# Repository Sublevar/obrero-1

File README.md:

# obrero-1

Secuenciador MIDI de pasos en Rust, con doble target: **ESP32** (MIDI DIN por UART) y **web** (WASM + Web MIDI API). Toda la lógica vive en un core portable; las plataformas solo aportan tiempo e I/O.

## Arquitectura

```
crates/obrero-core    Motor sans-io: parser MIDI, patrón, transporte, reloj 480 PPQN.
                      Sin threads ni I/O — la plataforma llama advance(now, lookahead)
                      y recibe eventos MIDI timestampeados. Testeable en host.
crates/obrero-wasm    Bindings wasm-bindgen del motor para el navegador.
web/                  UI TypeScript (vite): grilla de pasos, Web MIDI, scheduler
                      con lookahead de 100 ms y send timestampeado.
firmware/             Binario ESP32 (esp-idf-svc, toolchain xtensa propio).
                      Excluido del workspace raíz — se compila aparte.
```

- Reloj interno (master, emite 0xF8/Start/Stop) o externo (esclavo de MIDI clock entrante).
- Resolución interna 480 PPQN (ver "Resolución temporal"); el MIDI clock sigue a 24 PPQN y un paso de semicorchea = 120 ticks.
- `MIDI-DIN.md` documenta el hardware DIN (6N137, UART2 a 31250 bps).
- [PPQN](https://noiseengineering.us/blogs/loquelic-literitas-the-blog/getting-started-clocks/)
## Resolución temporal (PPQN)

PPQN (*pulses per quarter note*) es cuántos ticks internos caben en una negra: la grilla más fina en la que el motor puede ubicar una nota, medir un gate o repartir una subdivisión. El motor cuenta todo en ticks (`pattern::PPQN`, definido en `tuning.rs`); el tempo solo cambia cuánto dura cada tick.

Se fija en **480** porque es divisible por 24 (el MIDI clock sigue saliendo a 24 PPQN: un `0xF8` cada 20 ticks) y por 3, 4, 5, 8, 16…, así que tresillos, quintillos y micro-timing caen en ticks enteros. A 120 bpm un tick dura ~1,04 ms; a 300 bpm, ~208 µs.

Cuesta performance: a 300 bpm son 2400 ticks por segundo que el reloj genera y el motor procesa, y los rings (más abajo) crecen en proporción. El PPQN puede **reducirse** (p. ej. a 96 o 24) para ganar performance, sobre todo en el ESP32, a costa de granularidad y resolución del micro-timing. Debe seguir siendo múltiplo de 24; los demás topes se recalculan solos al cambiarlo.

## Ajustes (fine tuning)

Todas las variables de ajuste viven en `crates/obrero-core/src/tuning.rs`. Los tamaños de ring se derivan de las demás, así que cambiar una mantiene coherente al resto.

| Variable | Valor | Qué controla / qué pasa si se cambia |
|---|---|---|
| `PPQN` | 480 | Resolución interna. Más alto: más fino y más costoso. Debe ser múltiplo de `MIDI_CLOCK_PPQN`. |
| `MIDI_CLOCK_PPQN` | 24 | Resolución del `0xF8`. Fijada por el estándar MIDI. |
| `MIN_BPM` / `MAX_BPM` | 20 / 300 | Rango de tempo. `MAX_BPM` dimensiona los rings (peor caso). |
| `MAX_SUBS` | 32 | Suscripciones simultáneas a un `Clock`. Superado: `ClockError::Full`. |
| `PER_BAR_MAX` | 96 | Tope de `Subdivision::PerBar`. Dimensiona `NOTICE_CAPACITY`. |
| `EVERY_N_BARS_MAX` | 8 | Tope de `Subdivision::EveryNBars`. |
| `MAX_CATCHUP_US` | 100 000 | Atraso que el reloj recupera tick por tick. Más allá salta hacia adelante (`skipped_ticks`) en vez de emitir una ráfaga. |
| `MAX_LOOKAHEAD_US` | 100 000 | Lookahead por pasada que los rings cubren. `Engine::advance` parte lookaheads mayores en pasadas de este tamaño. La web usa 100 ms; el ESP32, 0. |
| `RING_MARGIN` | 4 | Holgura sumada al peor caso de cada ring, antes de redondear a potencia de 2. |
| `EXTERNAL_SMOOTHING` | 4 | Clock externo: el período entre `0xF8` se suaviza como `(anterior · (N − 1) + medido) / N`. Más alto filtra más jitter y sigue más lento los cambios de tempo. |
| `NOTICE_CAPACITY` | derivada (32) | Ring por defecto de una suscripción: avisos de `PerBar(PER_BAR_MAX)` en `MAX_CATCHUP_US + MAX_LOOKAHEAD_US` a `MAX_BPM`, redondeado a potencia de 2 (índice con máscara, sin división). 512 B por suscripción; se aloja al suscribir, no en el camino caliente. |
| `ENGINE_RING_CAPACITY` | derivada (512) | Ring de la suscripción del `Engine` (un aviso por tick base) en la misma ventana, potencia de 2: 8 KiB (16 B por aviso). Con estos topes no puede desbordar; `Engine::lost_ticks()` lo verifica y debe ser 0. |

Si un ring llega a llenarse, el aviso nuevo se descarta y se cuenta (`Subscription::take` devuelve los perdidos); nunca se pierde en silencio. Para un uso concreto se puede pedir otro tamaño con `Clock::subscribe_with_capacity` (se redondea a la siguiente potencia de 2).

La memoria la fija la ventana (`MAX_CATCHUP_US + MAX_LOOKAHEAD_US`), no el PPQN: duplicar la ventana duplica el ring del `Engine` (512 → 1024 → 2048 avisos, 8 → 16 → 32 KiB). En el ESP32-S3 conviene dejarla corta. El reloj externo (`0xF8`) también pasa por el `Clock`: el tempo se mide con el período entre pulsos y cada pulso reparte sus 20 ticks parejo, sin esperar al pulso siguiente.

## Workspace raíz (stable)

```sh
# Tests del motor (host)
cargo test -p obrero-core

# Build WASM
cargo build -p obrero-wasm --target wasm32-unknown-unknown
```

## Web

Requiere `wasm-pack` (`cargo install wasm-pack`) y Node.

```sh
cd web
npm install
npm run wasm   # compila crates/obrero-wasm → web/src/pkg
npm run dev    # http://localhost:5173 (Web MIDI requiere Chrome/Edge)
```

Elegí una salida MIDI (sintetizador, DAW o loopback virtual) y dale Play. Para modo esclavo, seleccioná una entrada MIDI y reloj "Externo".

## Firmware ESP32

Tiene su propio toolchain (`esp`, fork Xtensa — ver `firmware/rust-toolchain.toml`) y ESP-IDF v5.3.3 via embuild.

```sh
# Setup (una vez)
cargo install espup && espup install
source ~/export-esp.sh   # agregar al perfil de shell
cargo install espflash

cd firmware

cargo build              # primera build descarga ESP-IDF en .embuild/ — tarda
./dev.sh                 # build + flash + monitor por el conector UART del devkit

./dev.sh -p /dev/ttyUSB1 # elegir puerto serie a mano

./dev.sh -m esp32        # flashear el binario de la board ESP32 clásica

```

`dev.sh -m` solo elige qué directorio de target flashear — el chip compilado lo define `.cargo/config.toml`.

### USB-MIDI + debug serial (dos cables)

El firmware S3 levanta TinyUSB (componente `espressif/esp_tinyusb`, ver
`Cargo.toml` y `CONFIG_TINYUSB_MIDI_COUNT` en `sdkconfig.defaults`) sobre el
puerto **USB nativo** (GPIO19/20), que enumera como dispositivo USB-MIDI.
Los logs y el flasheo van por el conector **UART** (bridge USB-UART → UART0),
así que conviene tener ambos cables conectados: `dev.sh` flashea y monitorea
solo por `/dev/ttyUSB*` y deja el `/dev/ttyACM*` (USB nativo) libre para MIDI.

Al usar USB-OTG se pierde el USB-Serial-JTAG del puerto nativo (comparten PHY);
el debug queda en el conector UART. TinyUSB no compila para el ESP32 clásico
(no tiene USB-OTG): para ese chip hay que comentar el bloque
`extra_components` en `firmware/Cargo.toml`.

Flasheo manual según target activo:

```sh
# ESP32 (rev1)
espflash flash target/xtensa-esp32-espidf/debug/obrero-1 && espflash monitor

# ESP32-S3
espflash flash target/xtensa-esp32s3-espidf/debug/obrero-1 && espflash monitor
```

## Entorno de testeo

[Web MIDI Tester](https://studiocode.dev/webmidi-tester/midi)

## Licencia

[GPL-3.0-or-later](LICENSE) — © 2026 Pablo Labarta <pablitolabarta@gmail.com> & Santiago Fernandez <stfg.prof@gmail.com>.

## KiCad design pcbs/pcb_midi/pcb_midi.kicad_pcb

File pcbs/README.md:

Ajustar la configuración de backups (KiCad V10 o +)

En las versiones más recientes (KiCad V10), KiCad tiene un sistema de control de versiones local que crea la carpeta .history. Puedes desactivar esta función para que no se genere en primer lugar:

Abre KiCad y ve al menú Preferencias → Preferencias.
Busca la sección Control de versiones.
Desmarca la opción "Habilitar seguimiento Git" (o similar, "Enable Git tracking").
Ten en cuenta que, aunque desactives esta opción, es muy recomendable mantener la carpeta .history en tu .gitignore como respaldo.

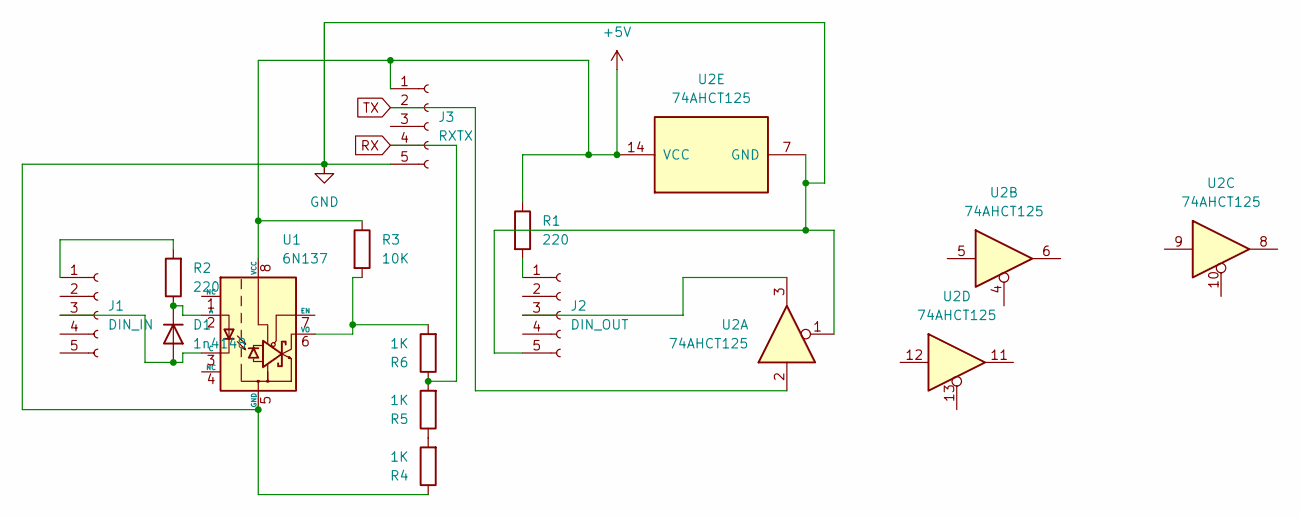
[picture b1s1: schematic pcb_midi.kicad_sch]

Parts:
D1: 1n4148; D_A-405_P10.16mm_Horizontal
J1: DIN_IN; JST_EH_B5B-EH-A_1x05_P2.50mm_Vertical
J2: DIN_OUT; JST_EH_B5B-EH-A_1x05_P2.50mm_Vertical
J3: RXTX; JST_EH_B5B-EH-A_1x05_P2.50mm_Vertical
R1: 220; R_Axial_DIN0207_L6.3mm_D2.5mm_P10.16mm_Horizontal
R2: 220; R_Axial_DIN0204_L3.6mm_D1.6mm_P7.62mm_Horizontal
R3: 10K; R_Axial_DIN0204_L3.6mm_D1.6mm_P7.62mm_Horizontal
R4, R5, R6: 1K; R_Axial_DIN0204_L3.6mm_D1.6mm_P7.62mm_Horizontal
U1: 6N137; DIP-8_W7.62mm
U2: 74AHCT125; DIP-14_W7.62mm_LongPads

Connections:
+5V: J3.1, R1.1, R3.1, U1.8 (VCC), U2.14 (VCC)
GND: J2.5, J3.5, R4.1, U1.5 (GND), U2.1, U2.7 (GND)
unnamed: D1.2 (A), J1.3, U1.3 (C)
unnamed: D1.1 (K), R2.1, U1.2 (A)
unnamed: J1.1, R2.2
unnamed: J2.1, R1.2
unnamed: J2.3, U2.3
unnamed: R4.2, R5.1
unnamed: R3.2, R6.2, U1.6 (VO)
RX: J3.4, R5.2, R6.1
TX: J3.2, U2.2

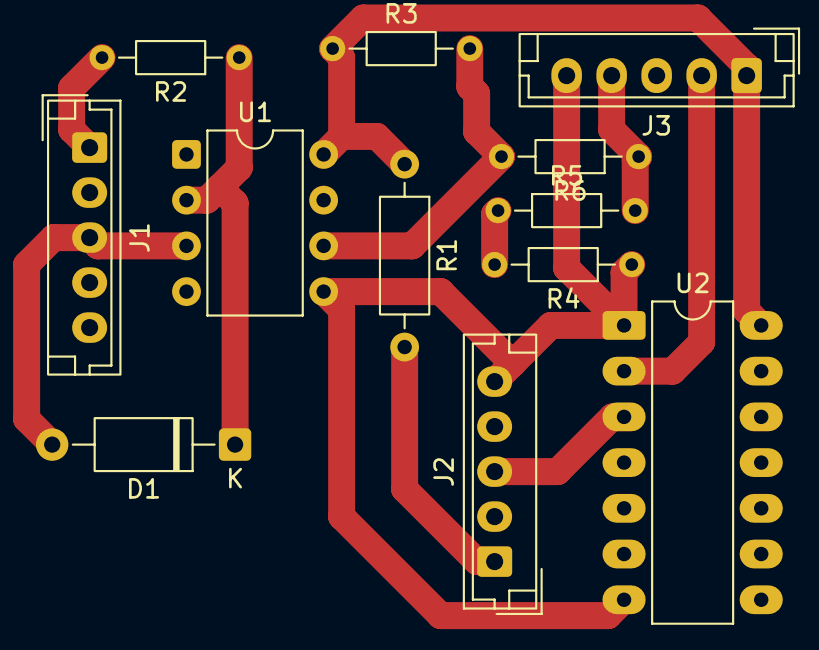
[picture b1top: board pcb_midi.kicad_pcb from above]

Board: 2 copper layers, 12 parts (0 on the bottom side), 11 nets.

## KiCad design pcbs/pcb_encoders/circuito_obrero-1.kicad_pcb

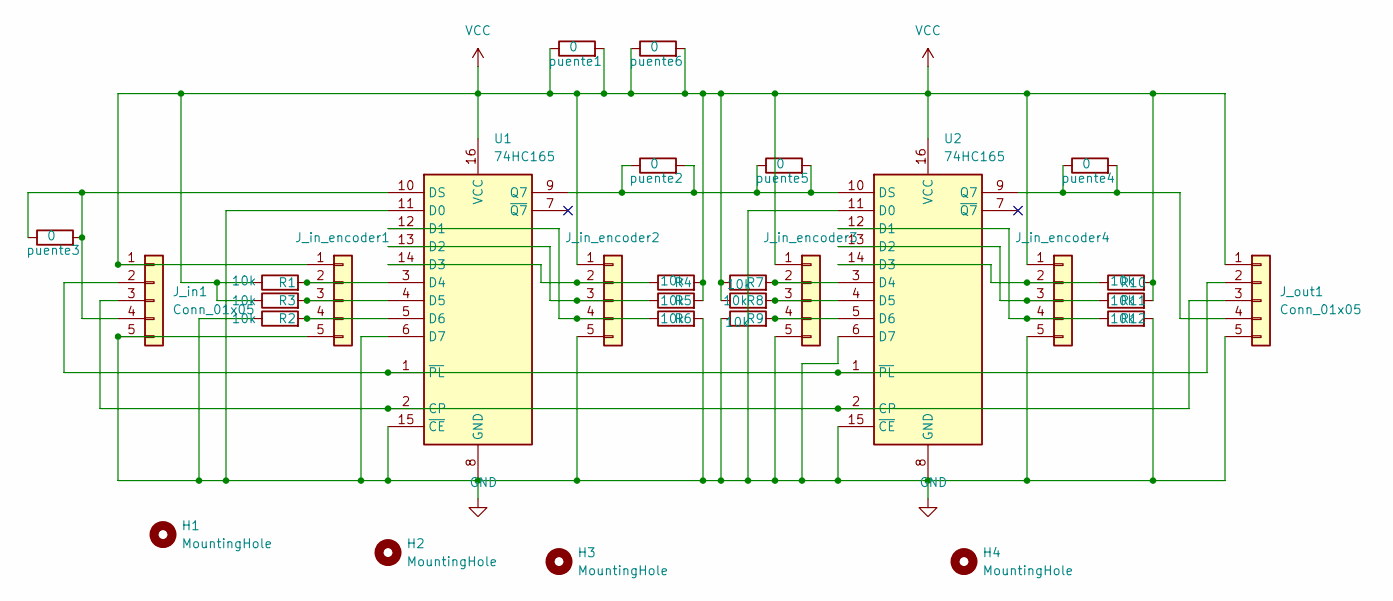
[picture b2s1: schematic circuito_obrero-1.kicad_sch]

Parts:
H1, H2, H3, H4: MountingHole; MountingHole_3.2mm_M3_DIN965
J_in1: Conn_01x05; JST_EH_B5B-EH-A_1x05_P2.50mm_Vertical
J_in_encoder1, J_in_encoder2, J_in_encoder3, J_in_encoder4: Conn_01x05; JST_EH_B5B-EH-A_1x05_P2.50mm_Vertical
J_out1: Conn_01x05; JST_EH_B5B-EH-A_1x05_P2.50mm_Vertical
R1, R2, R3, R4, R5, R6, R7, R8, R9, R10, R11, R12: 10k; R_Axial_DIN0204_L3.6mm_D1.6mm_P7.62mm_Horizontal
U1, U2: 74HC165; CERDIP-16_W7.62mm_SideBrazed_LongPads_Socket
puente1, puente2, puente3, puente4, puente5, puente6: 0; R_Axial_DIN0204_L3.6mm_D1.6mm_P7.62mm_Horizontal

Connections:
GND: J_in1.5, J_in_encoder1.5, J_in_encoder2.5, J_in_encoder3.5, J_in_encoder4.5, J_out1.5, R2.1, R6.2, R9.1, R12.2, U1.6 (D7), U1.8 (GND), U1.11 (D0), U1.15 (~CE), U2.6 (D7), U2.8 (GND), U2.11 (D0), U2.15 (~CE)
unnamed: J_in1.2, J_out1.2, U1.1 (~PL), U2.1 (~PL)
unnamed: J_in1.3, J_out1.3, U1.2 (CP), U2.2 (CP)
unnamed: J_in1.4, U1.10 (DS), puente3.1, puente3.2
unnamed: J_in_encoder1.2, R1.2, U1.3 (D4)
unnamed: J_in_encoder1.3, R3.2, U1.4 (D5)
unnamed: J_in_encoder1.4, R2.2, U1.5 (D6)
unnamed: J_in_encoder2.2, R4.1, U1.14 (D3)
unnamed: J_in_encoder2.3, R5.1, U1.13 (D2)
unnamed: J_in_encoder2.4, R6.1, U1.12 (D1)
unnamed: J_in_encoder3.2, R7.2, U2.3 (D4)
unnamed: J_in_encoder3.3, R8.2, U2.4 (D5)
unnamed: J_in_encoder3.4, R9.2, U2.5 (D6)
unnamed: J_in_encoder4.2, R10.1, U2.14 (D3)
unnamed: J_in_encoder4.3, R11.1, U2.13 (D2)
unnamed: J_in_encoder4.4, R12.1, U2.12 (D1)
unnamed: J_out1.4, U2.9 (Q7), puente4.1, puente4.2
unnamed: U1.9 (Q7), U2.10 (DS), puente2.1, puente2.2, puente5.1, puente5.2
VCC: J_in1.1, J_in_encoder1.1, J_in_encoder2.1, J_in_encoder3.1, J_in_encoder4.1, J_out1.1, R1.1, R3.1, R4.2, R5.2, R7.1, R8.1, R10.2, R11.2, U1.16 (VCC), U2.16 (VCC), puente1.1, puente1.2, puente6.1, puente6.2

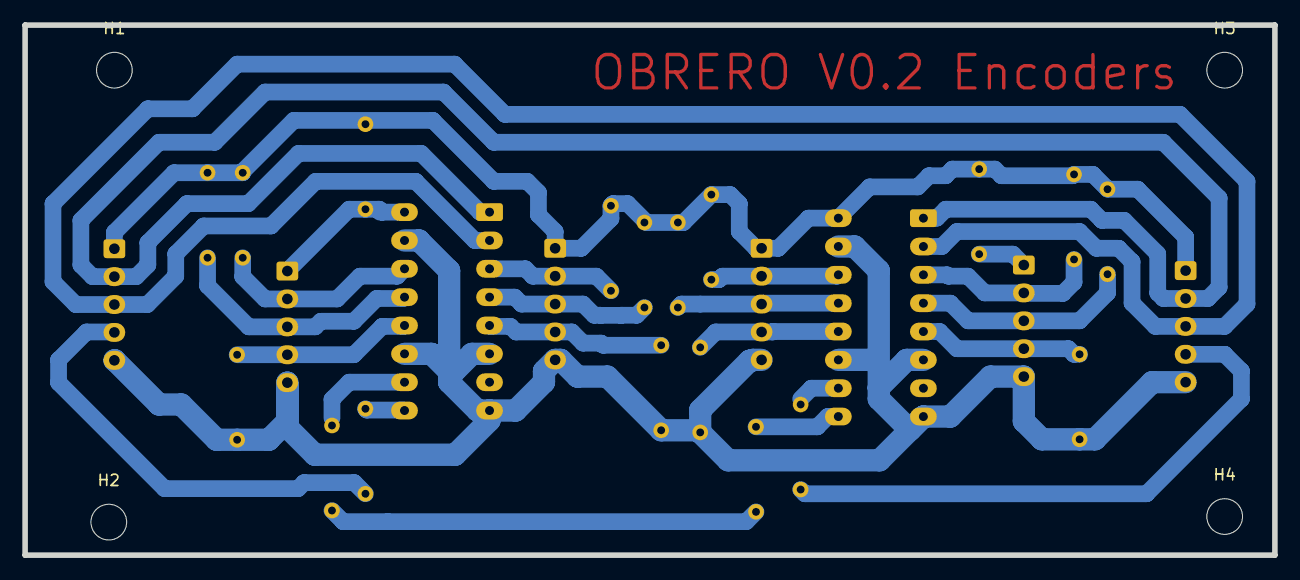
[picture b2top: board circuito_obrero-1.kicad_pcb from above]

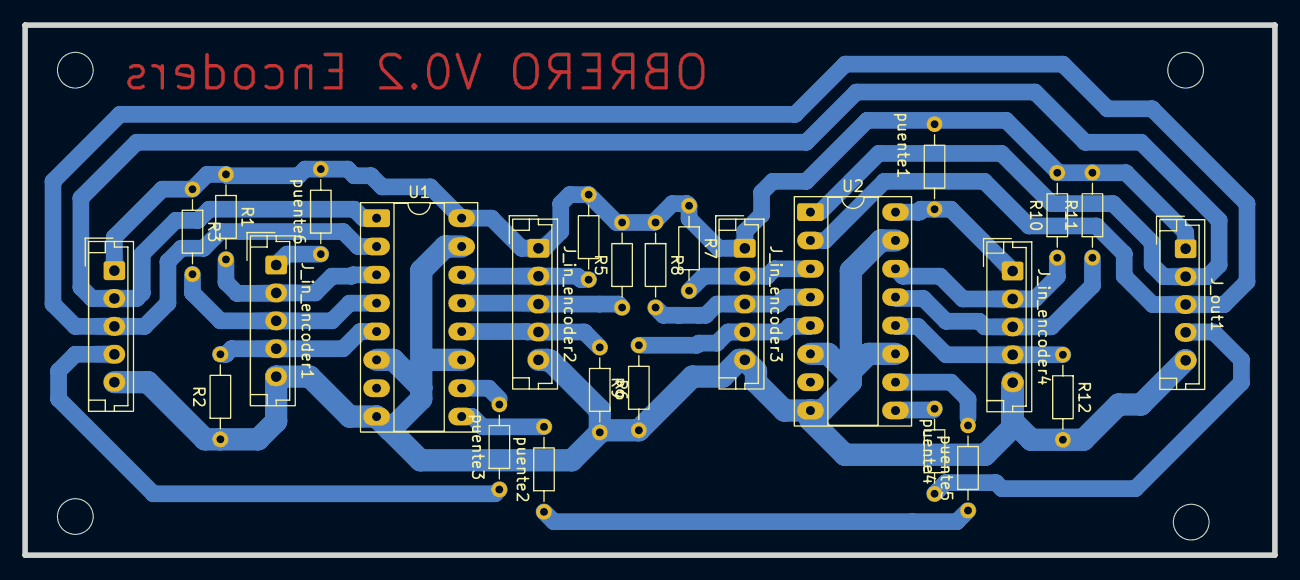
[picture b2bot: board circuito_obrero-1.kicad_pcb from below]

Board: 2 copper layers, 112.0 x 47.5 mm, 30 parts (26 on the bottom side), 19 nets.

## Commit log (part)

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2025-12-23 demo inciial
2026-04-10 README
2026-04-10 carguito nuevoo
2026-04-24 lecturas funcionales
2026-04-24 wip abstraccion de perifericos no funciona aun
2026-04-26 circuito :faltan rutas y cobres
2026-04-28 sumando resistencias al circuito
2026-05-01 agregadas las resis al circuito
2026-05-08 vcc funcional
2026-05-09 acomodando resistencias (revisar si es pull up o pull down el btn y los encoders)
2026-05-10 revision de resistencias y otros elementos: falta ruteo en el circuito
2026-05-13 preruteo: revisar y optimizar
2026-05-14 probando rerutear
2026-05-14 recableando mas prolijo
2026-05-15 pre añadir lagrimas
2026-05-15 circuito con lagrimas falta caminitos
2026-05-15 refinando borde
2026-05-15 redo de circuito 2 chip x 4 encoder
2026-05-15 circuito doble impresoin manual
2026-06-05 ajustes en en circuito
2026-06-06 entorno esp32s3
2026-06-10 cambios en el circuito
2026-06-10 refactor: web-v, obrero-core, firmware
2026-06-10 add: euclid & web-ui improvements
2026-06-10 env aun noo plenamente automatico, construccion de debug finio en proceso encorder leceen falal el circuito???
2026-06-10 add: license
2026-06-10 add: netlify deploy
2026-06-10 fix: basic responsive css
2026-06-12 leer 1 byte
2026-06-12 pines sueltos a gnd
2026-06-20 circuito impreso clean
2026-06-26 protocolo de control de calidad de encoders
2026-06-26 actualizando a esp32-s3 pinout
2026-06-26 WIP lectura de POTES
2026-06-28 fix de serial, lectuas viables, falta emprolijar bits y corroborar circutiso ( 1de 2 chips funcionales
